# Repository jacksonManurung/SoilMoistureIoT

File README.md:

# IoT Soil Moisture Sensor with STM32 & GSM Cloud Integration

## System Flow and Architecture

### Diagram koneksi keseluruhan sistem

### Disain koneksi microcontroller dan komponen pasif pendukungnya

### Disain modem dengan beberapa disain komponen pasif pendukungnya

### Disain "capacitor decoupling" untuk modem

### Disain konektor "SIM Card" untuk modem

### Disain indikator untuk modem

### Disain media penyimpanan menggunakan F-RAM

### Disain komponen aktif untuk backup system terpisah

### Disain antarmuka sensor

### Disain "multi-purpose" DC regulator dan juga battery power management system

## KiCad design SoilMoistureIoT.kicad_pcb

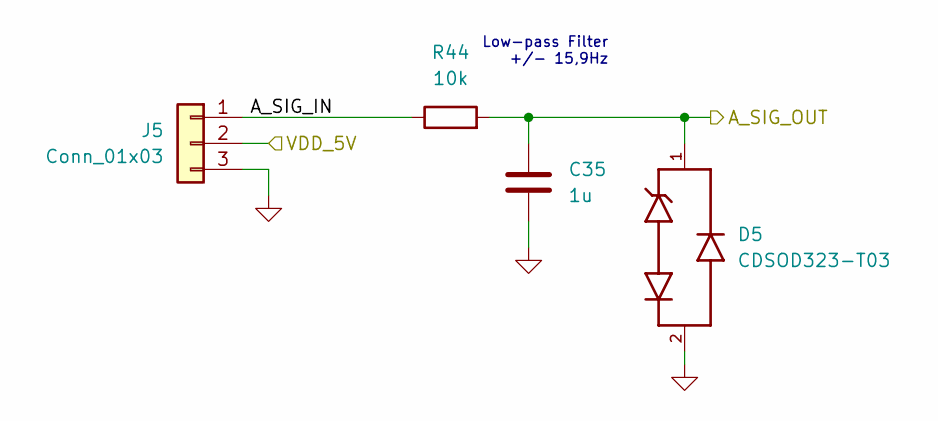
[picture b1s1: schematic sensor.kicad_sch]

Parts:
C35: 1u; C_0402_1005Metric
D5: CDSOD323-T03; SOD2513X114N; PARTREV 04/23
J5: Conn_01x03; JST_XA_S03B-XASK-1_1x03_P2.50mm_Horizontal
R44: 10k; R_0402_1005Metric

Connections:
/mcu/SENSE_IN: C35.1, D5.1, R44.2; also elsewhere on the board
/power_supply/VDD_5V: J5.2; also elsewhere on the board
/sensor/A_SIG_IN: J5.1, R44.1
GND: C35.2, D5.2, J5.3; also elsewhere on the board

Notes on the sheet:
Low-pass Filter +/- 15,9Hz

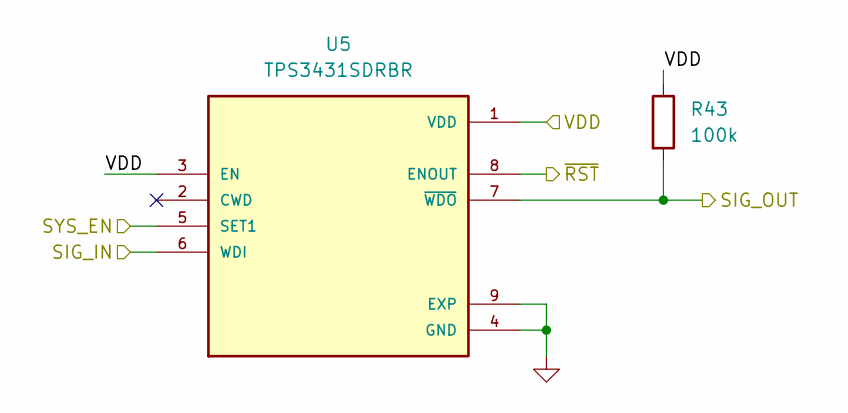
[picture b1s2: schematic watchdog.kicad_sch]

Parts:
R43: 100k; R_0402_1005Metric
U5: TPS3431SDRBR; IC_TPS3431SDRBR; PARTREV A

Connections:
/mcu/EWDG_EN: U5.5 (SET1); also elsewhere on the board
/mcu/EWDG_IN: R43.2, U5.7 (~WDO); also elsewhere on the board
/mcu/EWDG_OUT: U5.6 (WDI); also elsewhere on the board
/mcu/EWDG_~RST: U5.8 (ENOUT); also elsewhere on the board
/mcu/VDD: R43.1, U5.1 (VDD), U5.3 (EN); also elsewhere on the board
GND: U5.4 (GND), U5.9 (EXP); also elsewhere on the board

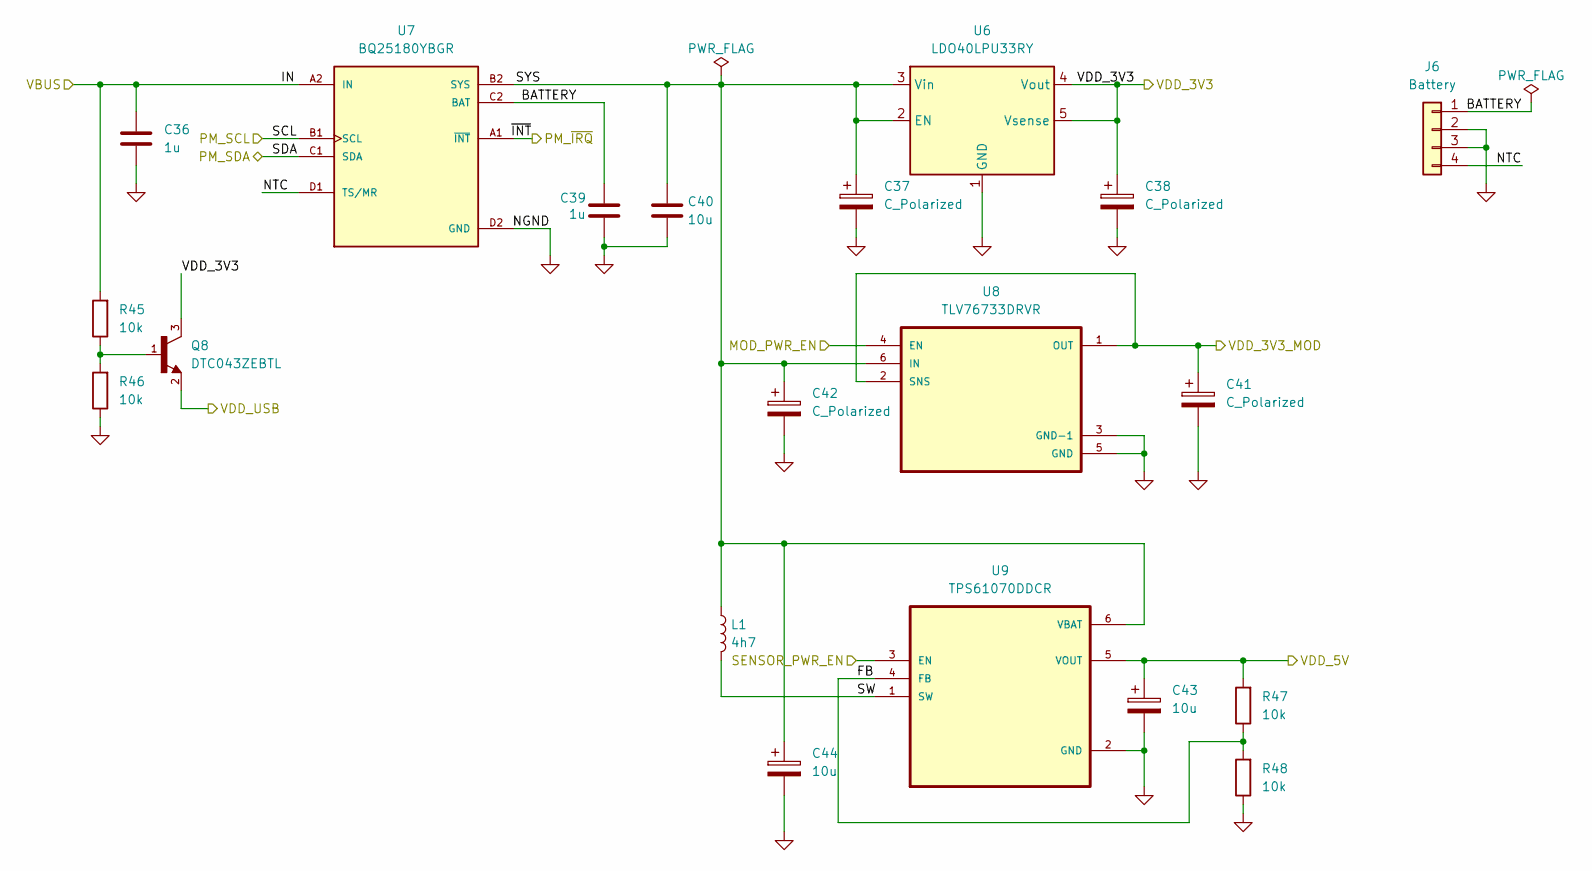
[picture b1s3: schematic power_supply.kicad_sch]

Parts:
C36, C39: 1u; C_0402_1005Metric
C37, C38, C41, C42: C_Polarized; CP_Elec_6.3x5.7
C40: 10u; C_0402_1005Metric
C43, C44: 10u; CP_Elec_6.3x5.7
J6: Battery; JST_XA_S04B-XASK-1N-BN_1x04_P2.50mm_Horizontal
L1: 4h7; L_APV_ANR5045
Q8: DTC043ZEBTL; SOTFL50P160X85-3N; PARTREV 002
R45, R46, R47, R48: 10k; R_0402_1005Metric
U6: LDO40LPU33RY; DFN-6-1EP_3x3mm_P0.95mm_EP1.7x2.6mm
U7: BQ25180YBGR; IC_BQ25180YBGR; PARTREV C
U8: TLV76733DRVR; SON65P200X200X80-7N
U9: TPS61070DDCR; SOT95P280X110-6N

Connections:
/mcu/MOD_PWR_EN: U8.4 (EN); also elsewhere on the board
/mcu/SENSE_PWR_EN: U9.3 (EN); also elsewhere on the board
/mcu/VDD: C38.1, Q8.3, U6.4 (Vout), U6.5 (Vsense); also elsewhere on the board
/mcu/VDDUSB: Q8.2; also elsewhere on the board
/modem/VBAT: C41.1, U8.1 (OUT), U8.2 (SNS); also elsewhere on the board
/power_supply/BATTERY: C39.1, J6.1, U7.C2 (BAT)
/power_supply/FB: R47.1, R48.2, U9.4 (FB)
/power_supply/IN: C36.1, R45.2, U7.A2 (IN); also elsewhere on the board
/power_supply/NTC: J6.4, U7.D1 (TS/MR)
/power_supply/SCL: U7.B1 (SCL); also elsewhere on the board
/power_supply/SDA: U7.C1 (SDA); also elsewhere on the board
/power_supply/SW: L1.2, U9.1 (SW)
/power_supply/SYS: C37.1, C40.1, C42.1, C44.1, L1.1, U6.2 (EN), U6.3 (Vin), U7.B2 (SYS), U8.6 (IN), U9.6 (VBAT)
/power_supply/VDD_5V: C43.1, R47.2, U9.5 (VOUT); also elsewhere on the board
/power_supply/~INT: U7.A1 (~INT); also elsewhere on the board
GND: C36.2, C37.2, C38.2, C39.2, C40.2, C41.2, C42.2, C43.2, C44.2, J6.2, J6.3, R46.1, R48.1, U6.1 (GND), U6.7 (GND), U7.D2 (GND), U8.3 (GND-1), U8.5 (GND), U9.2 (GND); also elsewhere on the board
unnamed: Q8.1, R45.1, R46.2

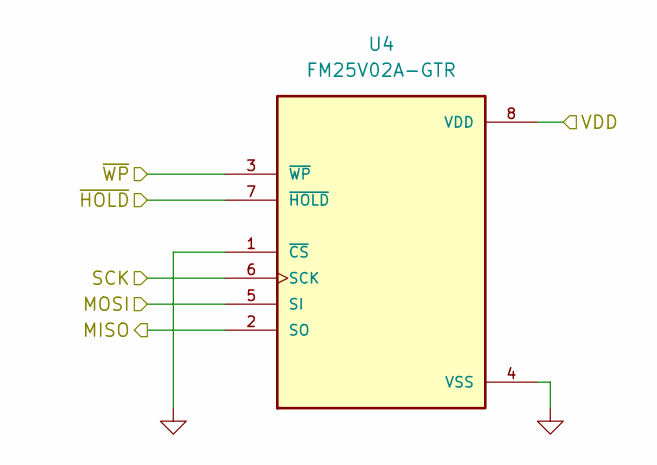
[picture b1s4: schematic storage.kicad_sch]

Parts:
U4: FM25V02A-GTR; SOIC127P602X172-8N

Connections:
/mcu/STR_MISO: U4.2 (SO); also elsewhere on the board
/mcu/STR_MOSI: U4.5 (SI); also elsewhere on the board
/mcu/STR_SCK: U4.6 (SCK); also elsewhere on the board
/mcu/STR_~HOLD: U4.7 (~HOLD); also elsewhere on the board
/mcu/STR_~WP: U4.3 (~WP); also elsewhere on the board
/mcu/VDD: U4.8 (VDD); also elsewhere on the board
GND: U4.1 (~CS), U4.4 (VSS); also elsewhere on the board

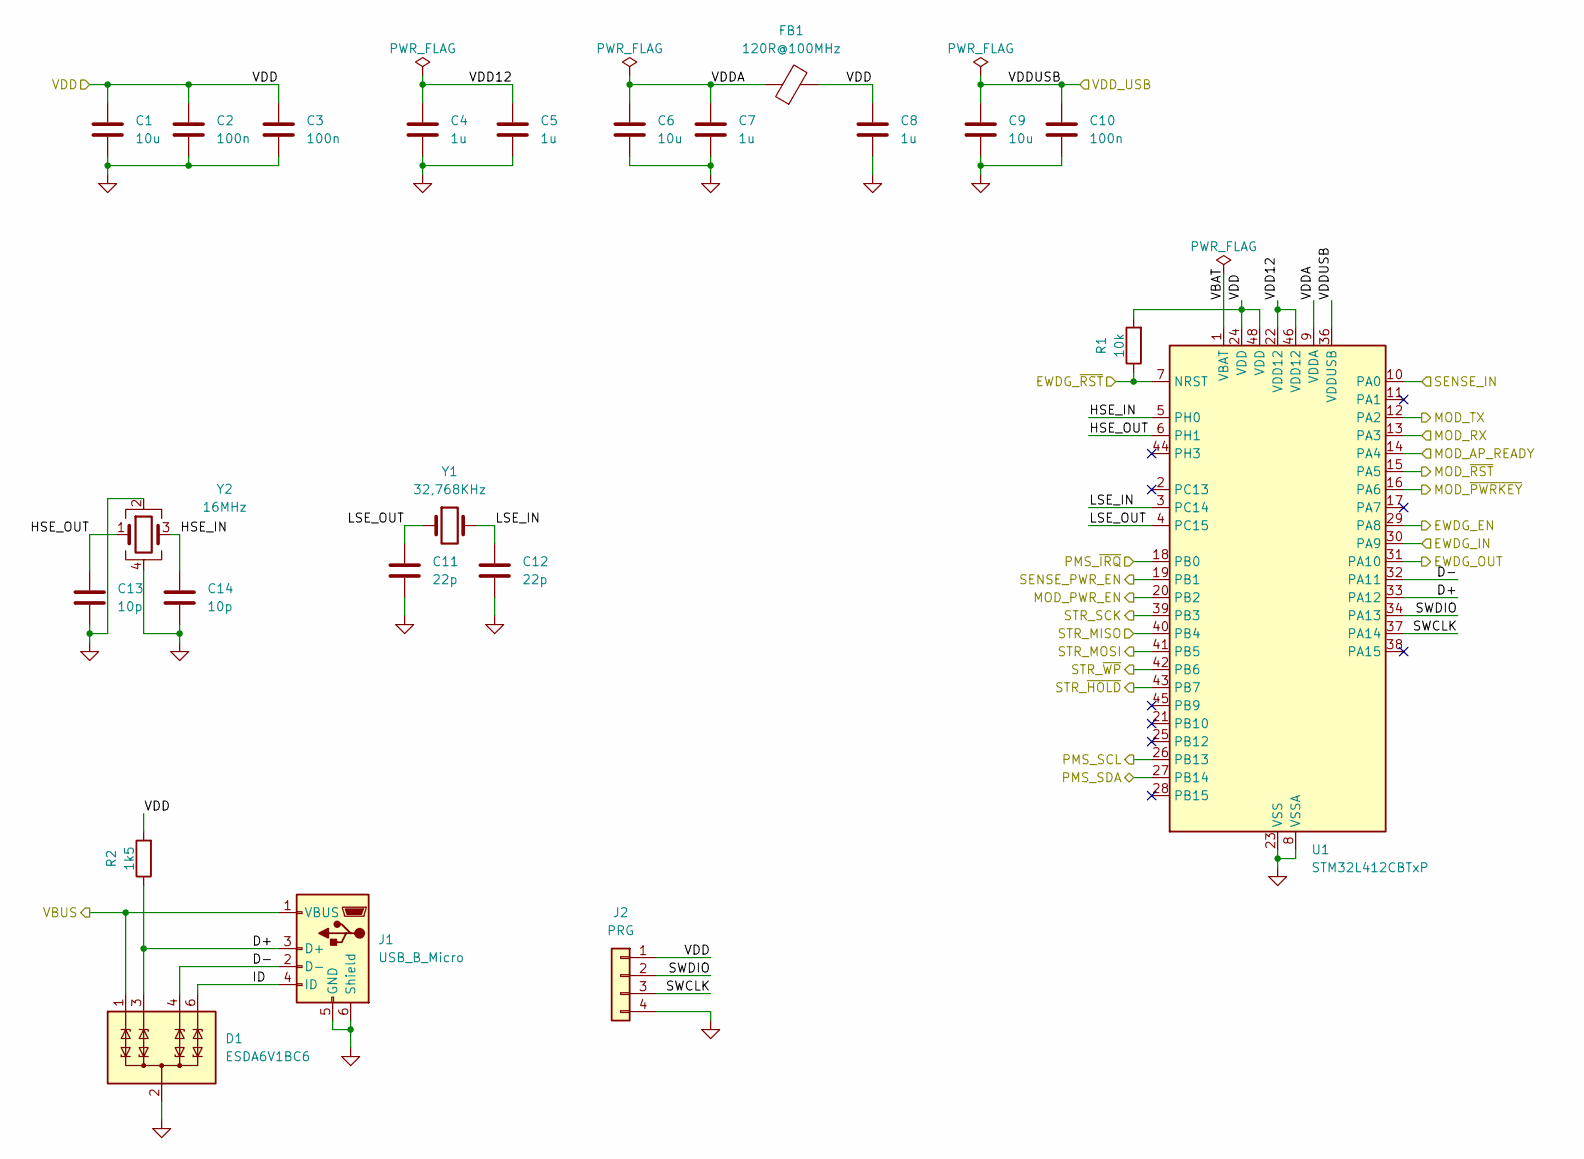
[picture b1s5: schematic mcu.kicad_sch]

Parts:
C1, C6, C9: 10u; C_0402_1005Metric
C2, C3, C10: 100n; C_0402_1005Metric
C4, C5, C7, C8: 1u; C_0402_1005Metric
C11, C12: 22p; C_0402_1005Metric
C13, C14: 10p; C_0402_1005Metric
D1: ESDA6V1BC6; SOT-23-6
FB1: 120R@100MHz; L_0805_2012Metric
J1: USB_B_Micro; USB_Micro-B_Wuerth_629105150521
J2: PRG; PinHeader_1x04_P2.54mm_Vertical
R1: 10k; R_0402_1005Metric
R2: 1k5; R_0402_1005Metric
U1: STM32L412CBTxP; LQFP-48_7x7mm_P0.5mm
Y1: 32,768KHz; Crystal_SMD_3215-2Pin_3.2x1.5mm
Y2: 16MHz; Crystal_SMD_3225-4Pin_3.2x2.5mm

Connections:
/mcu/D+: D1.3 (TVS2), J1.3 (D+), R2.1, U1.33 (PA12)
/mcu/D-: D1.4 (TVS3), J1.2 (D-), U1.32 (PA11)
/mcu/EWDG_EN: U1.29 (PA8); also elsewhere on the board
/mcu/EWDG_IN: U1.30 (PA9); also elsewhere on the board
/mcu/EWDG_OUT: U1.31 (PA10); also elsewhere on the board
/mcu/EWDG_~RST: R1.1, U1.7 (NRST); also elsewhere on the board
/mcu/HSE_IN: C14.1, U1.5 (PH0), Y2.3
/mcu/HSE_OUT: C13.1, U1.6 (PH1), Y2.1
/mcu/ID: D1.6 (TVS4), J1.4 (ID)
/mcu/LSE_IN: C12.1, U1.3 (PC14), Y1.2
/mcu/LSE_OUT: C11.1, U1.4 (PC15), Y1.1
/mcu/MOD_AP_READY: U1.14 (PA4); also elsewhere on the board
/mcu/MOD_PWR_EN: U1.20 (PB2); also elsewhere on the board
/mcu/MOD_RX: U1.13 (PA3); also elsewhere on the board
/mcu/MOD_TX: U1.12 (PA2); also elsewhere on the board
/mcu/MOD_~PWRKEY: U1.16 (PA6); also elsewhere on the board
/mcu/MOD_~RST: U1.15 (PA5); also elsewhere on the board
/mcu/SENSE_IN: U1.10 (PA0); also elsewhere on the board
/mcu/SENSE_PWR_EN: U1.19 (PB1); also elsewhere on the board
/mcu/STR_MISO: U1.40 (PB4); also elsewhere on the board
/mcu/STR_MOSI: U1.41 (PB5); also elsewhere on the board
/mcu/STR_SCK: U1.39 (PB3); also elsewhere on the board
/mcu/STR_~HOLD: U1.43 (PB7); also elsewhere on the board
/mcu/STR_~WP: U1.42 (PB6); also elsewhere on the board
/mcu/SWCLK: J2.3, U1.37 (PA14)
/mcu/SWDIO: J2.2, U1.34 (PA13)
/mcu/VBAT: U1.1 (VBAT)
/mcu/VDD: C1.1, C2.1, C3.1, C8.1, FB1.2, J2.1, R1.2, R2.2, U1.24 (VDD), U1.48 (VDD); also elsewhere on the board
/mcu/VDD12: C4.1, C5.1, U1.22 (VDD12), U1.46 (VDD12)
/mcu/VDDA: C6.1, C7.1, FB1.1, U1.9 (VDDA)
/mcu/VDDUSB: C9.1, C10.1, U1.36 (VDDUSB); also elsewhere on the board
/power_supply/IN: D1.1 (TVS1), J1.1 (VBUS); also elsewhere on the board
/power_supply/SCL: U1.26 (PB13); also elsewhere on the board
/power_supply/SDA: U1.27 (PB14); also elsewhere on the board
/power_supply/~INT: U1.18 (PB0); also elsewhere on the board
GND: C1.2, C2.2, C3.2, C4.2, C5.2, C6.2, C7.2, C8.2, C9.2, C10.2, C11.2, C12.2, C13.2, C14.2, D1.2 (COM), D1.5 (COM), J1.5 (GND), J1.6 (Shield), J2.4, U1.8 (VSSA), U1.23 (VSS), U1.35 (VSS), U1.47 (VSS), Y2.2, Y2.4; also elsewhere on the board

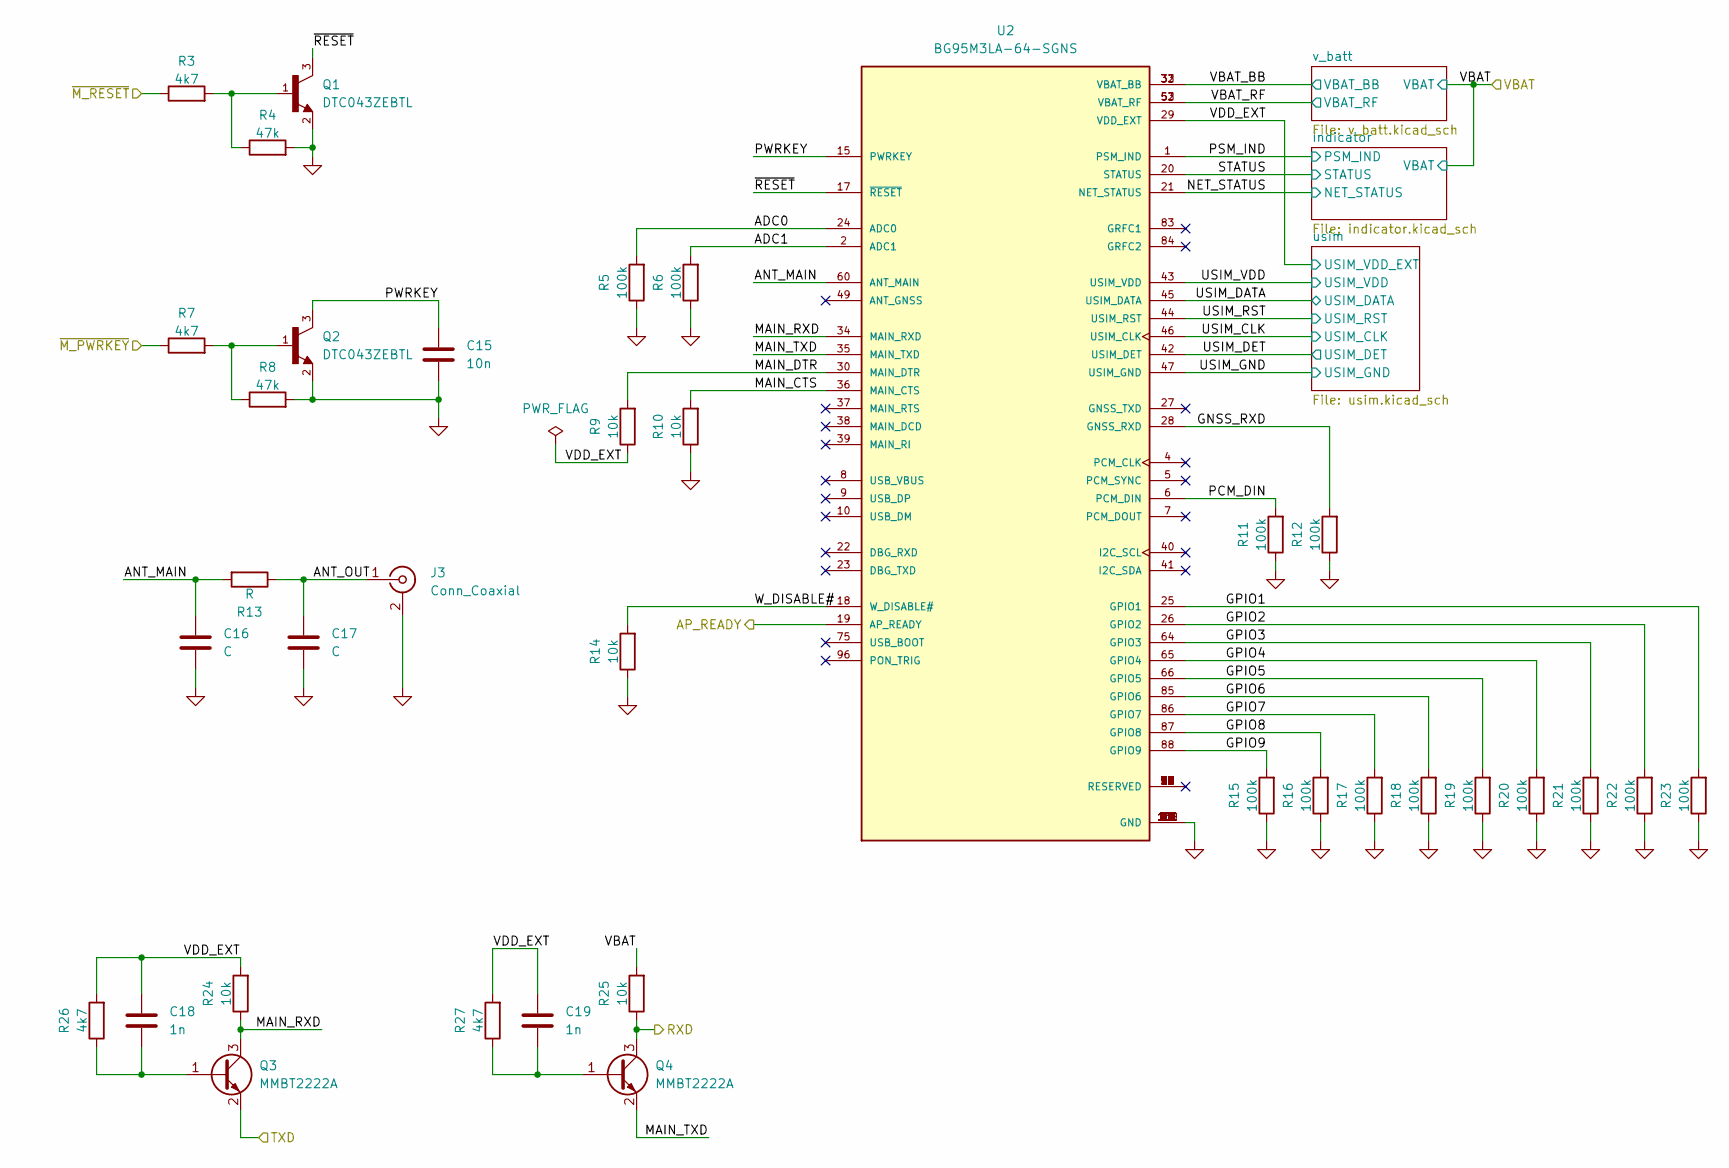
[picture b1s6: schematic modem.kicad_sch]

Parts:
C15: 10n; C_0402_1005Metric
C16, C17: C; C_0402_1005Metric
C18, C19: 1n; C_0402_1005Metric
J3: Conn_Coaxial; U.FL_Hirose_U.FL-R-SMT-1_Vertical
Q1, Q2: DTC043ZEBTL; SOTFL50P160X85-3N; PARTREV 002
Q3, Q4: MMBT2222A; SOT-23
R3, R7, R26, R27: 4k7; R_0402_1005Metric
R4, R8: 47k; R_0402_1005Metric
R5, R6, R11, R12, R15, R16, R17, R18, R19, R20, R21, R22, R23: 100k; R_0402_1005Metric
R9, R10, R14, R24, R25: 10k; R_0402_1005Metric
R13: R; R_0402_1005Metric
U2: BG95M3LA-64-SGNS; XCVR_BG95M3LA-64-SGNS

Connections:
/mcu/MOD_AP_READY: U2.19 (AP_READY); also elsewhere on the board
/mcu/MOD_RX: Q4.3 (C), R25.1; also elsewhere on the board
/mcu/MOD_TX: Q3.2 (E); also elsewhere on the board
/mcu/MOD_~PWRKEY: R7.1; also elsewhere on the board
/mcu/MOD_~RST: R3.1; also elsewhere on the board
/modem/ADC0: R5.2, U2.24 (ADC0)
/modem/ADC1: R6.2, U2.2 (ADC1)
/modem/ANT_MAIN: C16.1, R13.2, U2.60 (ANT_MAIN)
/modem/ANT_OUT: C17.1, J3.1 (In), R13.1
/modem/GNSS_RXD: R12.2, U2.28 (GNSS_RXD)
/modem/GPIO1: R23.2, U2.25 (GPIO1)
/modem/GPIO2: R22.2, U2.26 (GPIO2)
/modem/GPIO3: R21.2, U2.64 (GPIO3)
/modem/GPIO4: R20.2, U2.65 (GPIO4)
/modem/GPIO5: R19.2, U2.66 (GPIO5)
/modem/GPIO6: R18.2, U2.85 (GPIO6)
/modem/GPIO7: R17.2, U2.86 (GPIO7)
/modem/GPIO8: R16.2, U2.87 (GPIO8)
/modem/GPIO9: R15.2, U2.88 (GPIO9)
/modem/MAIN_CTS: R10.2, U2.36 (MAIN_CTS)
/modem/MAIN_DTR: R9.2, U2.30 (MAIN_DTR)
/modem/MAIN_RXD: Q3.3 (C), R24.1, U2.34 (MAIN_RXD)
/modem/MAIN_TXD: Q4.2 (E), U2.35 (MAIN_TXD)
/modem/NET_STATUS: U2.21 (NET_STATUS); also elsewhere on the board
/modem/PCM_DIN: R11.2, U2.6 (PCM_DIN)
/modem/PSM_IND: U2.1 (PSM_IND); also elsewhere on the board
/modem/PWRKEY: C15.1, Q2.3, U2.15 (PWRKEY)
/modem/STATUS: U2.20 (STATUS); also elsewhere on the board
/modem/USIM_CLK: U2.46 (USIM_CLK); also elsewhere on the board
/modem/USIM_DATA: U2.45 (USIM_DATA); also elsewhere on the board
/modem/USIM_DET: U2.42 (USIM_DET); also elsewhere on the board
/modem/USIM_RST: U2.44 (USIM_RST); also elsewhere on the board
/modem/USIM_VDD: U2.43 (USIM_VDD); also elsewhere on the board
/modem/VBAT: R25.2; also elsewhere on the board
/modem/VBAT_BB: U2.32 (VBAT_BB), U2.33 (VBAT_BB); also elsewhere on the board
/modem/VBAT_RF: U2.52 (VBAT_RF), U2.53 (VBAT_RF); also elsewhere on the board
/modem/VDD_EXT: C18.1, C19.1, R9.1, R24.2, R26.2, R27.2, U2.29 (VDD_EXT); also elsewhere on the board
/modem/W_DISABLE#: R14.2, U2.18 (W_DISABLE#)
/modem/~RESET: Q1.3, U2.17 (~RESET)
GND: C15.2, C16.2, C17.2, J3.2 (Ext), Q1.2, Q2.2, R4.2, R5.1, R6.1, R8.2, R10.1, R11.1, R12.1, R14.1, R15.1, R16.1, R17.1, R18.1, R19.1, R20.1, R21.1, R22.1, R23.1, U2.3 (GND), U2.31 (GND), U2.47 (USIM_GND), U2.48 (GND), U2.50 (GND), U2.54 (GND), U2.55 (GND), U2.58 (GND), U2.59 (GND), U2.61 (GND), U2.62 (GND), U2.67 (GND), U2.68 (GND), U2.69 (GND), U2.70 (GND), U2.71 (GND), U2.72 (GND), U2.73 (GND), U2.74 (GND), U2.79 (GND), U2.80 (GND), U2.81 (GND), U2.82 (GND), U2.89 (GND), U2.90 (GND), U2.91 (GND), U2.100 (GND), U2.101 (GND), U2.102 (GND); also elsewhere on the board
unnamed: Q1.1, R3.2, R4.1
unnamed: Q2.1, R7.2, R8.1
unnamed: C18.2, Q3.1 (B), R26.1
unnamed: C19.2, Q4.1 (B), R27.1

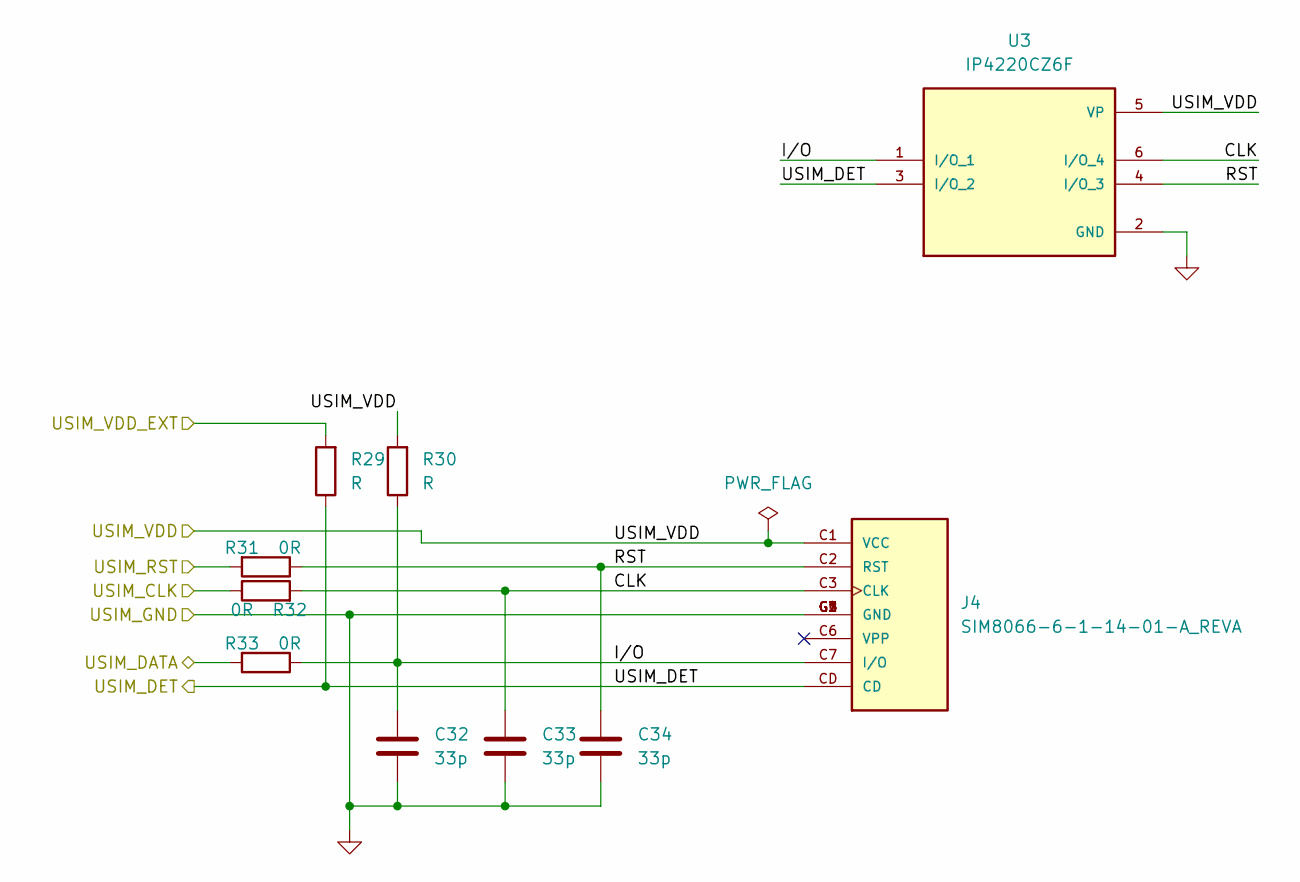
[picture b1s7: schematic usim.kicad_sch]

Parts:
C32, C33, C34: 33p; C_0402_1005Metric
J4: SIM8066-6-1-14-01-A_REVA; GCT_SIM8066-6-1-14-01-A_REVA; PARTREV REVA
R29, R30: R; R_0402_1005Metric
R31, R32, R33: 0R; R_0402_1005Metric
U3: IP4220CZ6F; SOT95P275X110-6N; PARTREV 5

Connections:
/modem/USIM_CLK: R32.1; also elsewhere on the board
/modem/USIM_DATA: R33.2; also elsewhere on the board
/modem/USIM_DET: J4.CD, R29.1, U3.3 (I/O_2); also elsewhere on the board
/modem/USIM_RST: R31.2; also elsewhere on the board
/modem/USIM_VDD: J4.C1 (VCC), R30.2, U3.5 (VP); also elsewhere on the board
/modem/VDD_EXT: R29.2; also elsewhere on the board
/modem/usim/CLK: C33.1, J4.C3 (CLK), R32.2, U3.6 (I/O_4)
/modem/usim/RST: C34.1, J4.C2 (RST), R31.1, U3.4 (I/O_3)
GND: C32.2, C33.2, C34.2, J4.C5 (GND), J4.G1 (GND), J4.G2 (GND), J4.G3 (GND), J4.G4 (GND), U3.2 (GND); also elsewhere on the board

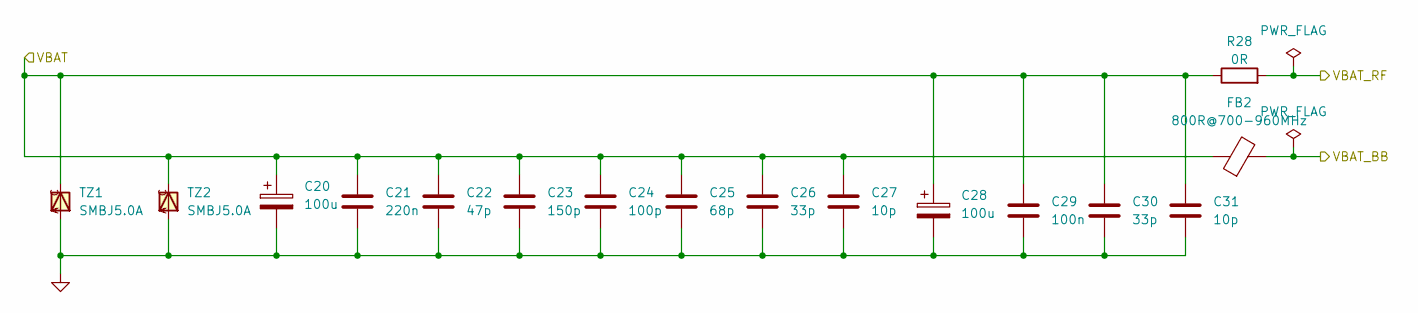
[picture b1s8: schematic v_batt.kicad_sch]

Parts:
C20, C28: 100u; CP_Elec_6.3x5.4
C21: 220n; C_0402_1005Metric
C22: 47p; C_0402_1005Metric
C23: 150p; C_0402_1005Metric
C24: 100p; C_0402_1005Metric
C25: 68p; C_0402_1005Metric
C26, C30: 33p; C_0402_1005Metric
C27, C31: 10p; C_0402_1005Metric
C29: 100n; C_0402_1005Metric
FB2: 800R@700-960MHz; L_0805_2012Metric
R28: 0R; R_0402_1005Metric
TZ1, TZ2: SMBJ5.0A; SMB

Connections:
/modem/VBAT: C20.1, C21.1, C22.1, C23.1, C24.1, C25.1, C26.1, C27.1, C28.1, C29.1, C30.1, C31.1, FB2.1, R28.1, TZ1.C, TZ2.C; also elsewhere on the board
/modem/VBAT_BB: FB2.2; also elsewhere on the board
/modem/VBAT_RF: R28.2; also elsewhere on the board
GND: C20.2, C21.2, C22.2, C23.2, C24.2, C25.2, C26.2, C27.2, C28.2, C29.2, C30.2, C31.2, TZ1.A, TZ2.A; also elsewhere on the board

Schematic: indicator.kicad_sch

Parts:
D2, D3, D4: LED; LED_0603_1608Metric
Q5, Q6, Q7: MMBT2222A; SOT-23
R34, R35, R36: 2k2; R_0402_1005Metric
R37, R38, R39: 4k7; R_0402_1005Metric
R40, R41, R42: 47k; R_0402_1005Metric

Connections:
/modem/NET_STATUS: R39.2; also elsewhere on the board
/modem/PSM_IND: R37.2; also elsewhere on the board
/modem/STATUS: R38.2; also elsewhere on the board
/modem/VBAT: D2.2 (A), D3.2 (A), D4.2 (A); also elsewhere on the board
GND: Q5.2 (E), Q6.2 (E), Q7.2 (E), R40.1, R41.1, R42.1; also elsewhere on the board
unnamed: D2.1 (K), R34.2
unnamed: D3.1 (K), R35.2
unnamed: D4.1 (K), R36.2
unnamed: Q5.1 (B), R37.1, R40.2
unnamed: Q5.3 (C), R34.1
unnamed: Q6.1 (B), R38.1, R41.2
unnamed: Q6.3 (C), R35.1
unnamed: Q7.1 (B), R39.1, R42.2
unnamed: Q7.3 (C), R36.1

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
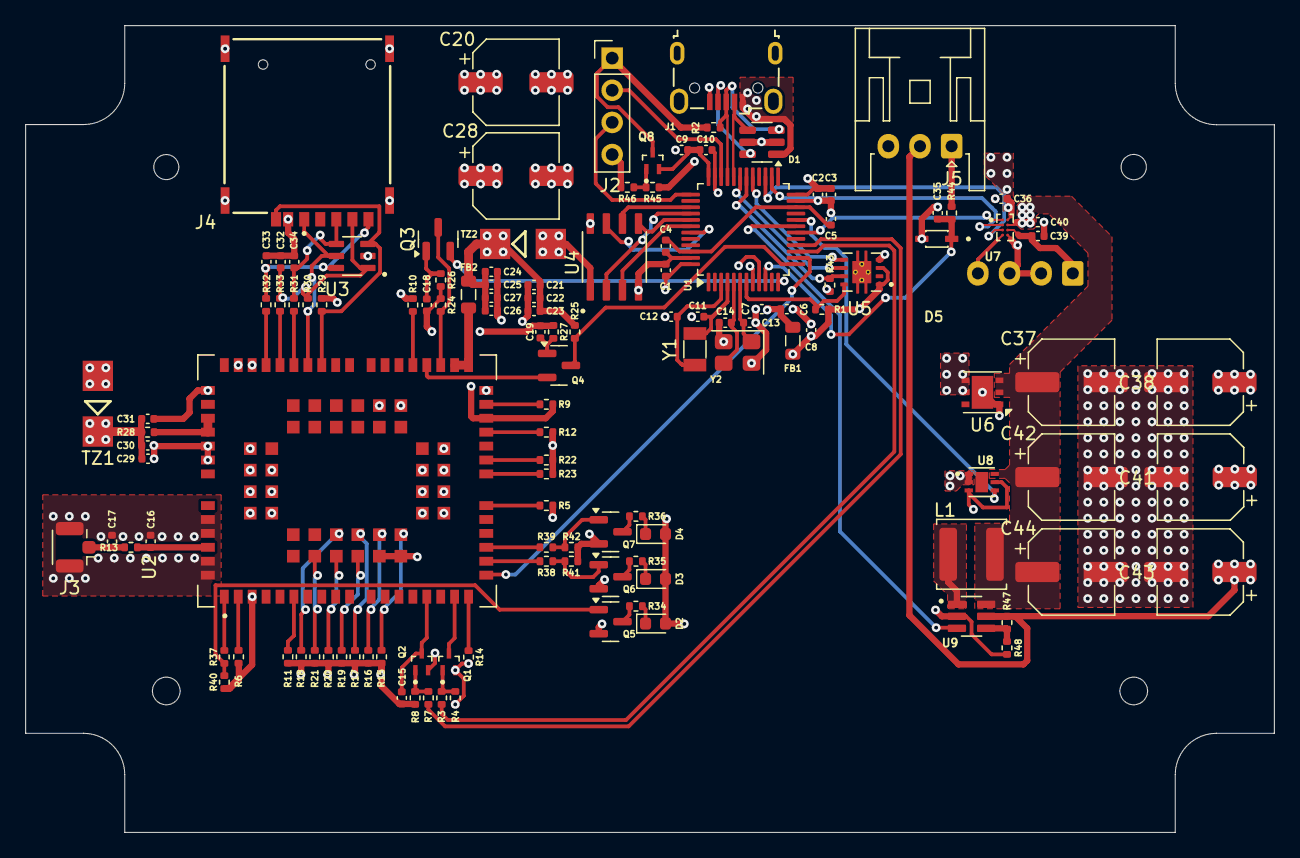
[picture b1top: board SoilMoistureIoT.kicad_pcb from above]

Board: 4 copper layers, 98.7 x 63.8 mm, 127 parts (1 on the bottom side), 93 nets.

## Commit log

2025-08-29 initial project
2025-09-01 adding some component
2025-09-02 Layout was finish
2025-09-03 Create README.md
    first commit Readme.md
2025-09-10 adding datasheet
2025-09-10 Create README.md
    rebuilt Readme.md
